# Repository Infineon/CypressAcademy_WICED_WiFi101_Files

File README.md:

# CypressAcademy_WW101_Files
#
# This contains files used in the WICED WiFi 101 class
#
# A video version of the class can be found at www.cypress.com/training/wicedwifi-101

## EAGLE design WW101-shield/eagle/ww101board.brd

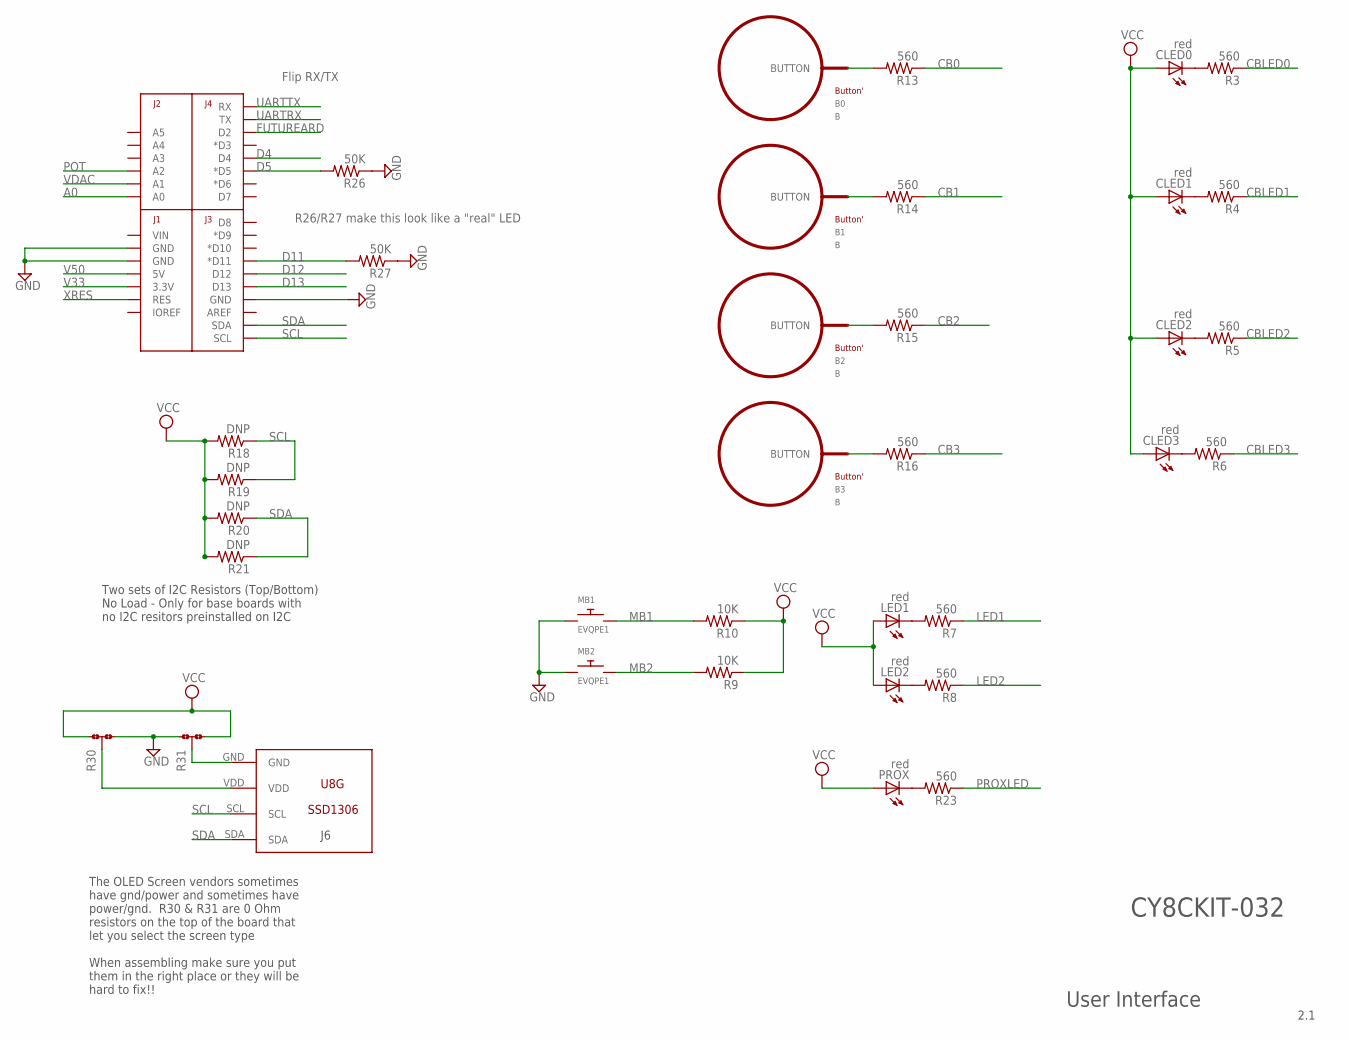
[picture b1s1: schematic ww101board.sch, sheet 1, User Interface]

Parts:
B0, B1, B2, B3: B; BUTTON_PASSIVE_10MM
CLED0, CLED1, CLED2, CLED3: red; CHIP-LED0603
J6: U8G-096-OLED; 096-SSD1306
LED1, LED2: red; CHIP-LED0603
MB1, MB2: EVQPE1; SWITCH
PROX: red; CHIP-LED0603
R3, R4, R5, R6, R7, R8, R13, R14, R15, R16, R23: 560; 0603-RES
R9, R10: 10K; 0603-RES
R18, R19, R20, R21: DNP; 0603-RES
R26, R27: 50K; 0603-RES
R30: JMP-3-1_2
R31: JMP-3-2_3
U$1: ARDUINO_R3_SHIELDNOLABELS; UNO_R3_SHIELD_NOLABELS

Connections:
A0: U$1.A0; also elsewhere on the board
CB0: R13.1; also elsewhere on the board
CB1: R14.1; also elsewhere on the board
CB2: R15.1; also elsewhere on the board
CB3: R16.1; also elsewhere on the board
CBLED0: R3.1; also elsewhere on the board
CBLED1: R4.1; also elsewhere on the board
CBLED2: R5.1; also elsewhere on the board
CBLED3: R6.1; also elsewhere on the board
D4: U$1.D4; also elsewhere on the board
D5: R26.2, U$1.D5 (*D5); also elsewhere on the board
D11: R27.2, U$1.D11 (*D11); also elsewhere on the board
D12: U$1.D12; also elsewhere on the board
D13: U$1.D13; also elsewhere on the board
FUTUREARD: U$1.D2; also elsewhere on the board
GND: MB1.P$1, MB2.P$1, R26.1, R27.1, R30.3, R31.1, U$1.GND@0 (GND), U$1.GND@1 (GND), U$1.GND@2 (GND); also elsewhere on the board
LED1: R7.1; also elsewhere on the board
LED2: R8.1; also elsewhere on the board
MB1: MB1.P$2, R10.2; also elsewhere on the board
MB2: MB2.P$2, R9.2; also elsewhere on the board
unnamed: B0.BUTTON, R13.2
unnamed: PROX.C, R23.2
unnamed: B1.BUTTON, R14.2
unnamed: B2.BUTTON, R15.2
unnamed: CLED0.C, R3.2
unnamed: CLED1.C, R4.2
unnamed: CLED2.C, R5.2
unnamed: CLED3.C, R6.2
unnamed: LED1.C, R7.2
unnamed: LED2.C, R8.2
unnamed: J6.VDD, R30.2
unnamed: B3.BUTTON, R16.2
unnamed: J6.GND, R31.2
POT: U$1.A2; also elsewhere on the board
PROXLED: R23.1; also elsewhere on the board
SCL: J6.SCL, R18.1, R19.1, U$1.SCL; also elsewhere on the board
SDA: J6.SDA, R20.1, R21.1, U$1.SDA; also elsewhere on the board
UARTRX: U$1.TX; also elsewhere on the board
UARTTX: U$1.RX; also elsewhere on the board
V33: U$1.3.3V; also elsewhere on the board
V50: U$1.5V; also elsewhere on the board
VCC: CLED0.A, CLED1.A, CLED2.A, CLED3.A, LED1.A, LED2.A, PROX.A, R9.1, R10.1, R18.2, R19.2, R20.2, R21.2, R30.1, R31.3; also elsewhere on the board
VDAC: U$1.A1; also elsewhere on the board
XRES: U$1.RES; also elsewhere on the board

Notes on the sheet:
Flip RX/TX
User Interface
Two sets of I2C Resistors (Top/Bottom) No Load - Only for base boards with no I2C resitors preinstalled on I2C
The OLED Screen vendors sometimes have gnd/power and sometimes have power/gnd. R30 & R31 are 0 Ohm resistors on the top of the board that let you select the screen type When assembling make sure you put them in the right place or they will be hard to fix!!
2.1
CY8CKIT-032
R26/R27 make this look like a "real" LED

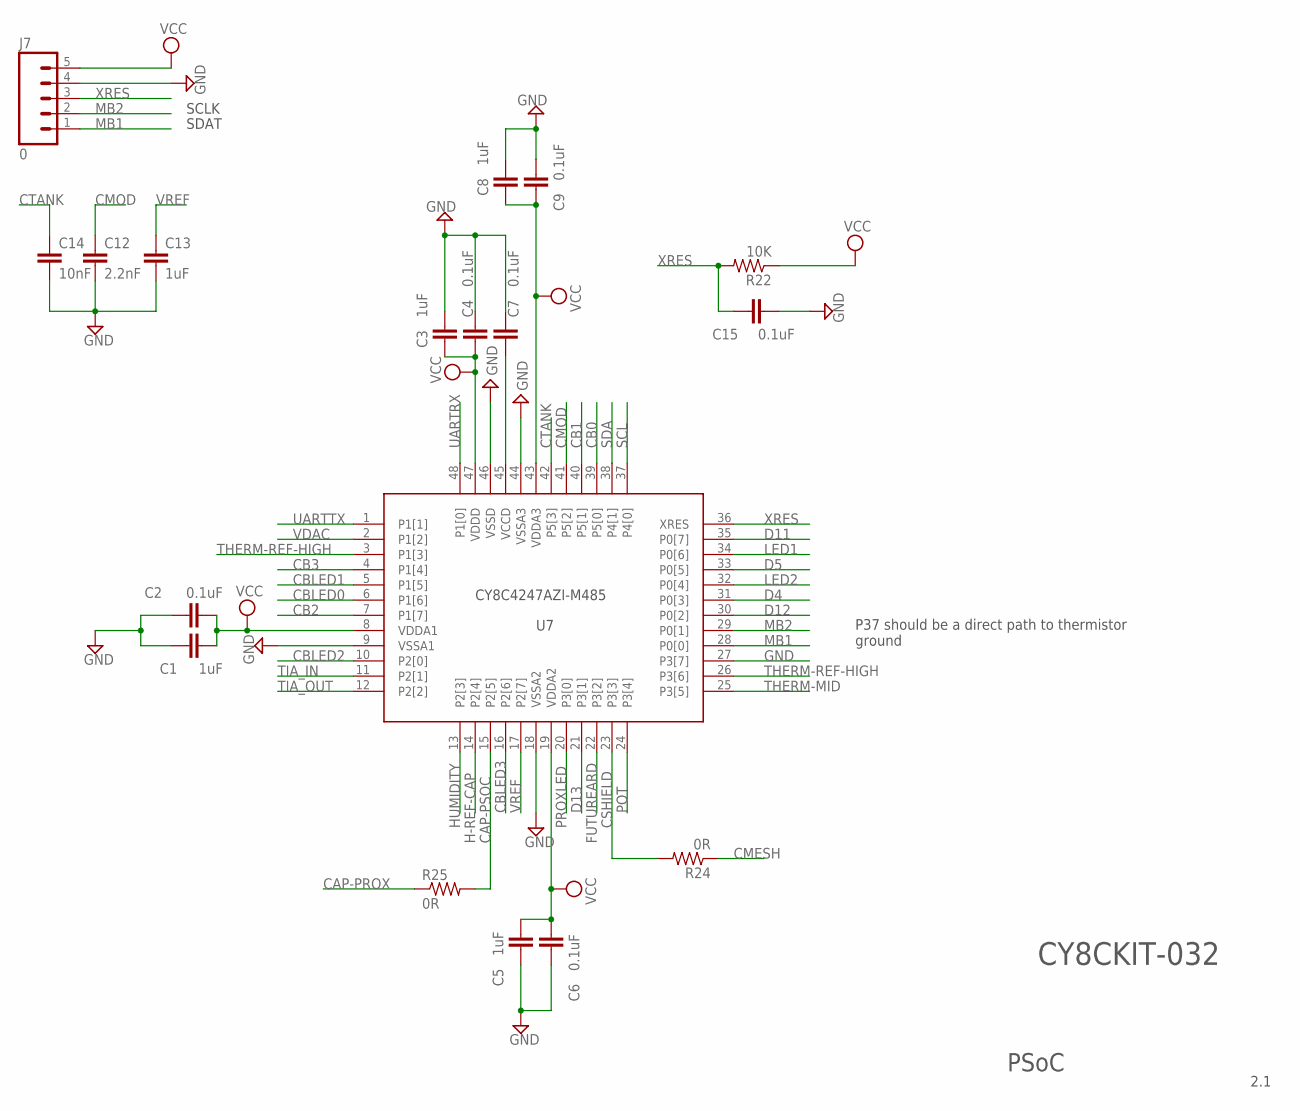
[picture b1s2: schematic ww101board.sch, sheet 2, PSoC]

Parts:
C1, C3, C5, C8, C13: 1uF; 0603-CAP
C2, C4, C6, C7, C9, C15: 0.1uF; 0603-CAP
C12: 2.2nF; 0603-CAP
C14: 10nF; 0603-CAP
J7: 0; 1X05_LOCK
R22: 10K; 0603-RES
R24, R25: 0R; 0603-RES
U7: CY8C4A45-48; TQFP-7X7-48
U$7: CYLOGO-SILK

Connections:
CAP-PROX: R25.1
CAP-PSOC: R25.2, U7.15 (P2[5])
CB0: U7.39 (P5[0]); also elsewhere on the board
CB1: U7.40 (P5[1]); also elsewhere on the board
CB2: U7.7 (P1[7]); also elsewhere on the board
CB3: U7.4 (P1[4]); also elsewhere on the board
CBLED0: U7.6 (P1[6]); also elsewhere on the board
CBLED1: U7.5 (P1[5]); also elsewhere on the board
CBLED2: U7.10 (P2[0]); also elsewhere on the board
CBLED3: U7.16 (P2[6]); also elsewhere on the board
CMESH: R24.1
CMOD: C12.1, U7.41 (P5[2])
CSHIELD: R24.2, U7.23 (P3[3])
CTANK: C14.1, U7.42 (P5[3])
D4: U7.31 (P0[3]); also elsewhere on the board
D5: U7.33 (P0[5]); also elsewhere on the board
D11: U7.35 (P0[7]); also elsewhere on the board
D12: U7.30 (P0[2]); also elsewhere on the board
D13: U7.21 (P3[1]); also elsewhere on the board
FUTUREARD: U7.22 (P3[2]); also elsewhere on the board
GND: C1.1, C2.1, C3.1, C4.1, C5.2, C6.2, C7.1, C8.1, C9.1, C12.2, C13.2, C14.2, C15.1, J7.4, U7.9 (VSSA1), U7.18 (VSSA2), U7.27 (P3[7]), U7.44 (VSSA3), U7.46 (VSSD); also elsewhere on the board
H-REF-CAP: U7.14 (P2[4]); also elsewhere on the board
HUMIDITY: U7.13 (P2[3]); also elsewhere on the board
LED1: U7.34 (P0[6]); also elsewhere on the board
LED2: U7.32 (P0[4]); also elsewhere on the board
MB1: J7.1, U7.28 (P0[0]); also elsewhere on the board
MB2: J7.2, U7.29 (P0[1]); also elsewhere on the board
unnamed: C7.2, U7.45 (VCCD)
POT: U7.24 (P3[4]); also elsewhere on the board
PROXLED: U7.20 (P3[0]); also elsewhere on the board
SCL: U7.37 (P4[0]); also elsewhere on the board
SDA: U7.38 (P4[1]); also elsewhere on the board
THERM-MID: U7.25 (P3[5]); also elsewhere on the board
THERM-REF-HIGH: U7.3 (P1[3]), U7.26 (P3[6]); also elsewhere on the board
TIA_IN: U7.11 (P2[1]); also elsewhere on the board
TIA_OUT: U7.12 (P2[2]); also elsewhere on the board
UARTRX: U7.48 (P1[0]); also elsewhere on the board
UARTTX: U7.1 (P1[1]); also elsewhere on the board
VCC: C1.2, C2.2, C3.2, C4.2, C5.1, C6.1, C8.2, C9.2, J7.5, R22.1, U7.8 (VDDA1), U7.19 (VDDA2), U7.43 (VDDA3), U7.47 (VDDD); also elsewhere on the board
VDAC: U7.2 (P1[2]); also elsewhere on the board
VREF: C13.1, U7.17 (P2[7])
XRES: C15.2, J7.3, R22.2, U7.36 (XRES); also elsewhere on the board

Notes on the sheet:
SCLK
SDAT
PSoC
2.1
CY8C4247AZI-M485
CY8CKIT-032
P37 should be a direct path to thermistor ground

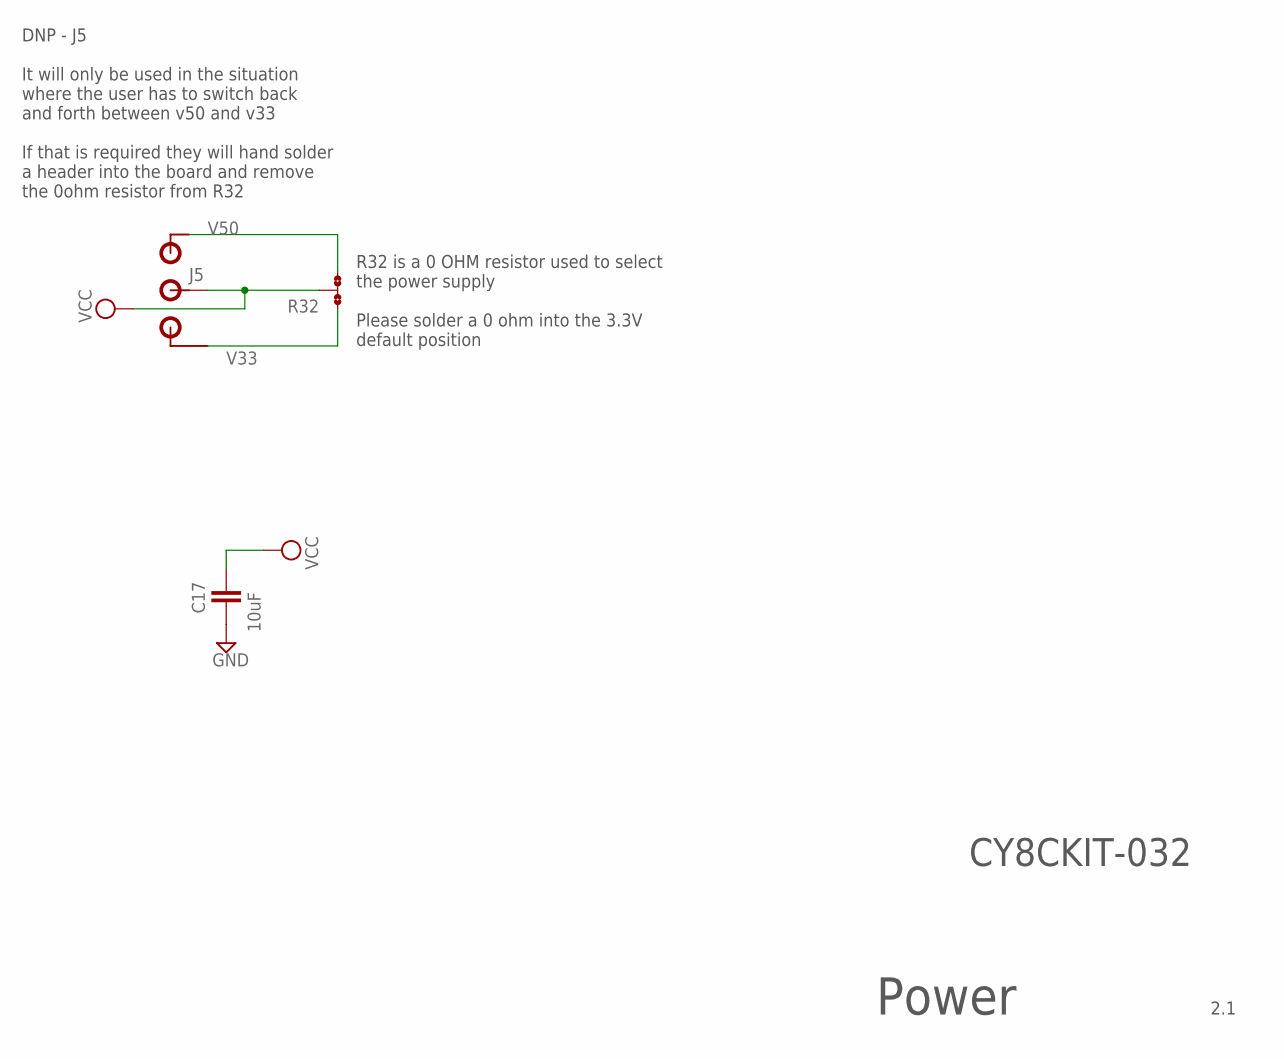
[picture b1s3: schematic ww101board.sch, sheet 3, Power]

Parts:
C17: 10uF; 0603-CAP
J5: JMP-3-PTH-PTH; JMP-3-NO-PTH-2.54
R32: JMP-3-NO

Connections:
GND: C17.2; also elsewhere on the board
V33: J5.3, R32.1; also elsewhere on the board
V50: J5.1, R32.3; also elsewhere on the board
VCC: C17.1, J5.2, R32.2; also elsewhere on the board

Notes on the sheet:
Power
2.1
DNP - J5 It will only be used in the situation where the user has to switch back and forth between v50 and v33 If that is required they will hand solder a header into the board and remove the 0ohm resistor from R32
R32 is a 0 OHM resistor used to select the power supply Please solder a 0 ohm into the 3.3V default position
CY8CKIT-032

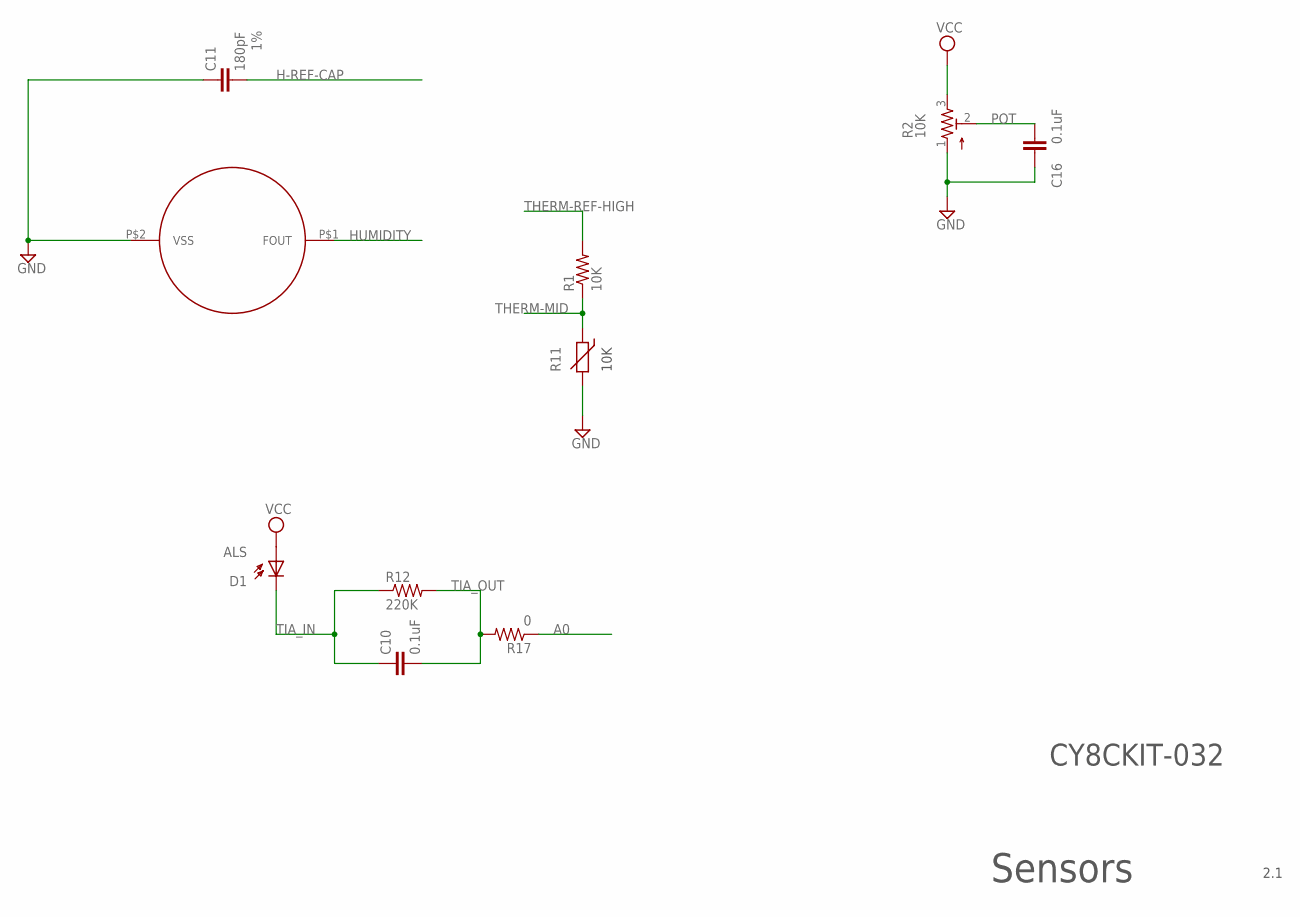
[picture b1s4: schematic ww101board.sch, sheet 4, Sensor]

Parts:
C10, C16: 0.1uF; 0603-CAP
C11: 180pF; 0603-CAP
D1: ALS
HUMIDITY: HPP801A031; HUMIDITY
R1: 10K; 0603-RES
R2: 10K; 3386P
R11: THERMISTOR-5; R-5
R12: 220K; 0603-RES
R17: 0; 0603-RES

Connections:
A0: R17.1; also elsewhere on the board
GND: C11.1, C16.2, HUMIDITY.P$2 (VSS), R2.1, R11.2; also elsewhere on the board
H-REF-CAP: C11.2; also elsewhere on the board
HUMIDITY: HUMIDITY.P$1 (FOUT); also elsewhere on the board
POT: C16.1, R2.2; also elsewhere on the board
THERM-MID: R1.1, R11.1; also elsewhere on the board
THERM-REF-HIGH: R1.2; also elsewhere on the board
TIA_IN: C10.1, D1.CATHODE (C1), R12.1; also elsewhere on the board
TIA_OUT: C10.2, R12.2, R17.2; also elsewhere on the board
VCC: D1.ANNODE (E1), R2.3; also elsewhere on the board

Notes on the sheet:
Sensors
10K
2.1
CY8CKIT-032

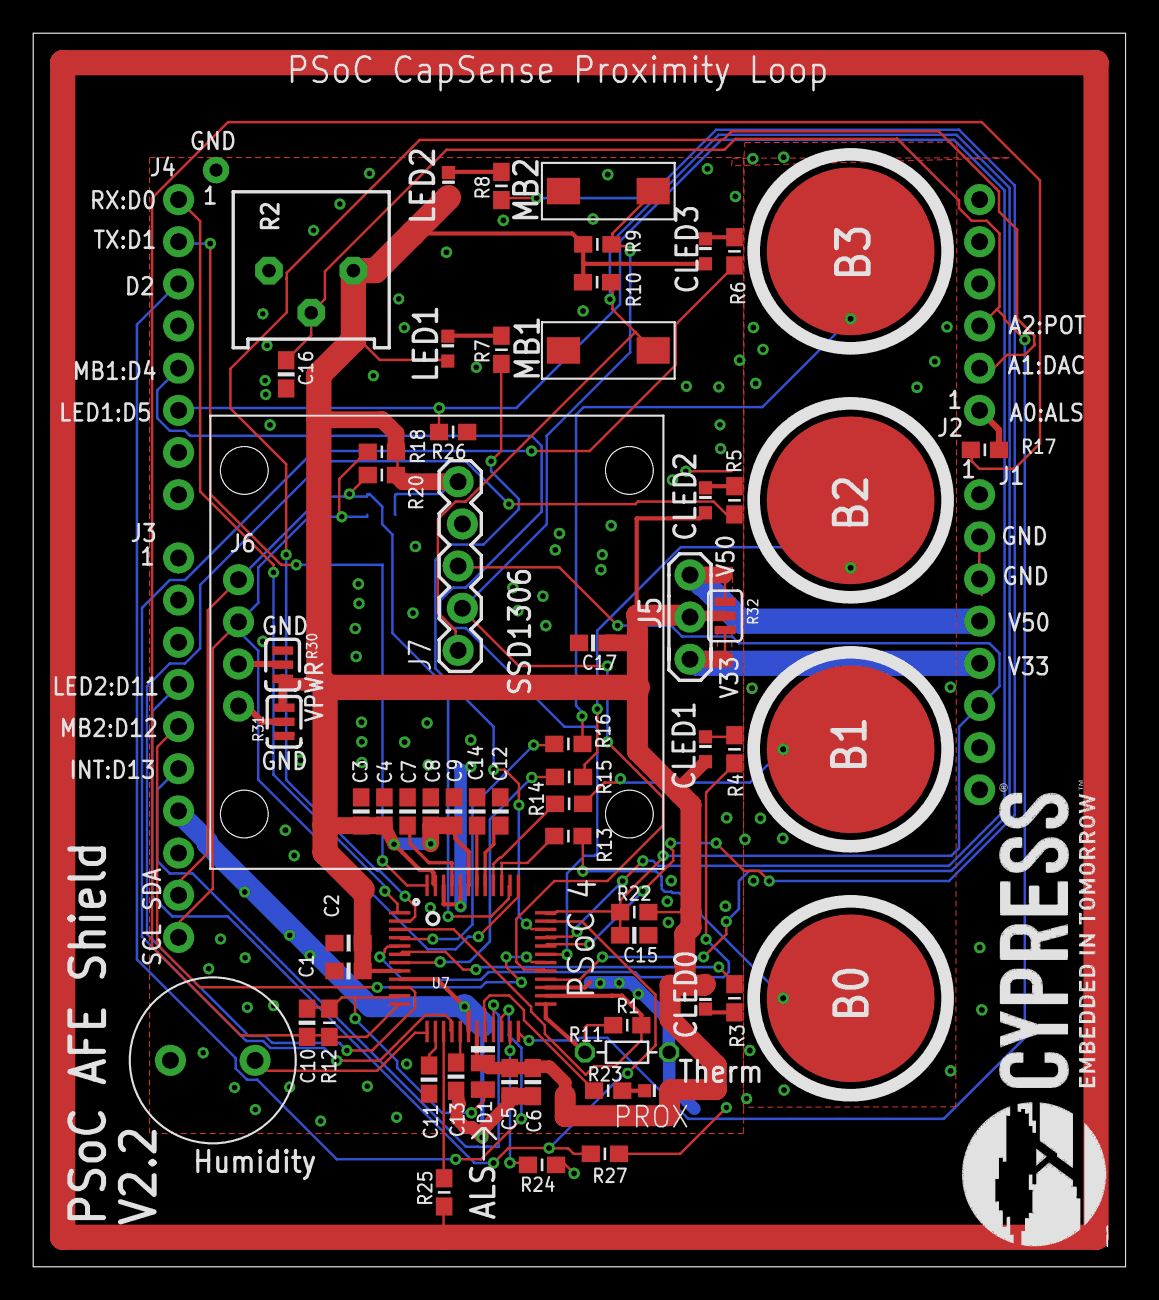
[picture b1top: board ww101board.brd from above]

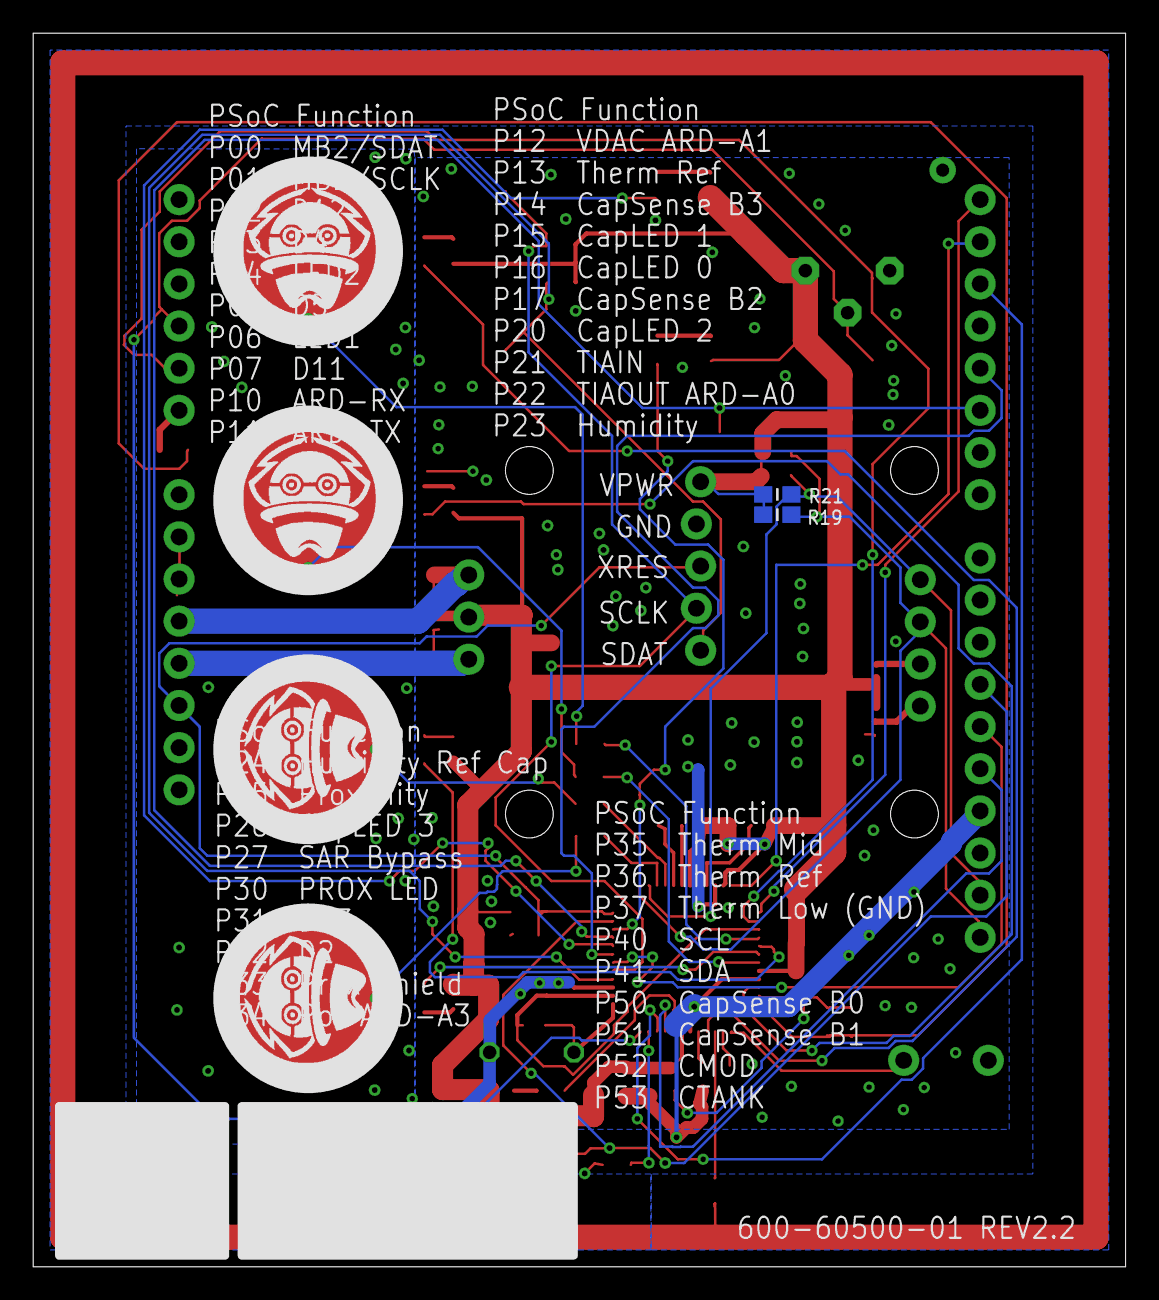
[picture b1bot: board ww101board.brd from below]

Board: 2 copper layers, 65.8 x 74.3 mm, 68 parts (2 on the bottom side), 56 nets.

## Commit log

2017-08-28 New README
2017-08-28 Add certificate files.
2017-08-28 Update readme contents.
2017-08-29 Initial checkin.
2017-09-27 Add CURL for Windows
2017-10-09 Update platform files for new shield
2017-10-09 Remove old shield firmware
2017-10-09 UPdate firmware to new pinout
2017-10-09 Files updated with new shield info, HTTP chapter and projects, and updated formatting of the manual.
2017-10-09 Fix project so that message is updated when waiting for connection.
2017-10-11 Fix project so that u8g2 library is inncluded. Take WW101 out of project names.
2017-10-11 Change project names
2017-10-11 Updated to latest board files and remove u8g lib from upper level.
2017-10-11 REmove certs from public git site.
2017-10-11 Remove class certs from public server.
2017-10-11 Fix project names for shield.
2017-10-16 Update FW for bootload entry using both buttons and POT. Update FW for auto-cal IDAC for humidity but manaual for buttons.
2017-10-17 Fix MB1/MB2 pin order. Refactor main.c to put each system processing into a separate function.
2017-10-18 Updates after beta class
2017-10-18 Fix typo
2017-10-24 Fix PWM error. Fix issue with initial I2C scan in weather station.
2017-10-25 Remove WiFi SSID and PW from material
2017-10-25 Update FW after updating formatting and comments.
2017-10-25 Update with link to video class
2017-10-26 Update project after fixing shield issues.
2017-10-30 Add version 1 platform files. Update schematics to latest version.
2017-10-30 ARH updates to manual
2017-10-30 Add new platform files for WICED 6.0
2017-10-30 fix board revision error
2017-10-30 replace platform files with corrected ones
2017-10-30 upate readme file
2017-10-30 Put comment in PWM file for shield V1
2017-10-31 minor update to http chapter
2017-11-02 Add solution for mqtt and http
2017-11-02 Update http and project chapter with latest info.
2017-11-02 Move cap on XRES to gnd, make holes larger for OLED and humidity sensor.
2017-11-02 move cap on xres to gnd
2017-12-05 Move certificate file up so that it doesn't already have the cert for httpbin.org
2017-12-06 Update chap 7 examples for new HTTP chapter. Rewrite HTTP chapter examples and make edits from SJ class.
2017-12-07 Make platform baseboard independent
2017-12-11 fix heading numbering
2017-12-13 Fix bugs in FW from BHAT OOB review. Clean up FW files.
2017-12-20 Update http projects to deal with server disconnect
2018-01-02 Update to check hostname for TLS connections.
2018-01-23 Update AWS for new account name.
2018-01-24 Rename projects for new exercise numbers
2018-01-25 Add V2.2 board files
2018-01-25 Checkin official kit firmware version
2018-01-25 Minor updates to manual
2018-02-01 Update material after MIT class in WW1805
2018-02-05 CHange name of survey to tour to avoid confusion with NPS.
2018-02-05 Improve comments regarding active high/low LED
2018-02-05 CHange survey to tour
2018-02-06 Minor format fixes.
2018-03-26 Update manuals after WW1811 and WW1813 classes. Split chapter 6 into 6a (sockets) and 6b (TLS)
2018-03-26 Update projects for WW1811 and WW1813. Split chapter 6. Simplify JSON projects.
2018-03-27 Fix typo in exercise 1
2018-03-28 Update AWS projects to explain that CLIENT_ID is the AWS thing name.
2018-06-25 Update WiFi SSID to new network name.
2018-06-25 Fix typo in server name.
2018-06-27 Fix changes related to 6.2
2018-06-27 Update for 6.2 libraries
2018-07-03 Updates from WW1826 class.
2018-08-07 Update manual to revision *B. Minor corrections from class in KYCC.
2018-09-22 Minor fixes and improvements to 7b and 7c exercises
2018-09-27 Fix incorrect PDF file checkin
2018-11-27 Update 7C to include AWS ATS root CA. Include separate document for back cover.
2019-02-07 Updates after KYCC and MIT classes.

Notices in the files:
parts and their libraries:
ww101board: License : http://creativecommons.org/licenses/by-sa/3.1/ (Creative Commons 3.1)
ww101board: License : http://creativecommons.org/licenses/by-sa/4.0
(Creative Commons 4.0)
